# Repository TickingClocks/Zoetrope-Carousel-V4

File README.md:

# Zoetrope-Carousel-V4
repository for the Zoetrope Carousel V4

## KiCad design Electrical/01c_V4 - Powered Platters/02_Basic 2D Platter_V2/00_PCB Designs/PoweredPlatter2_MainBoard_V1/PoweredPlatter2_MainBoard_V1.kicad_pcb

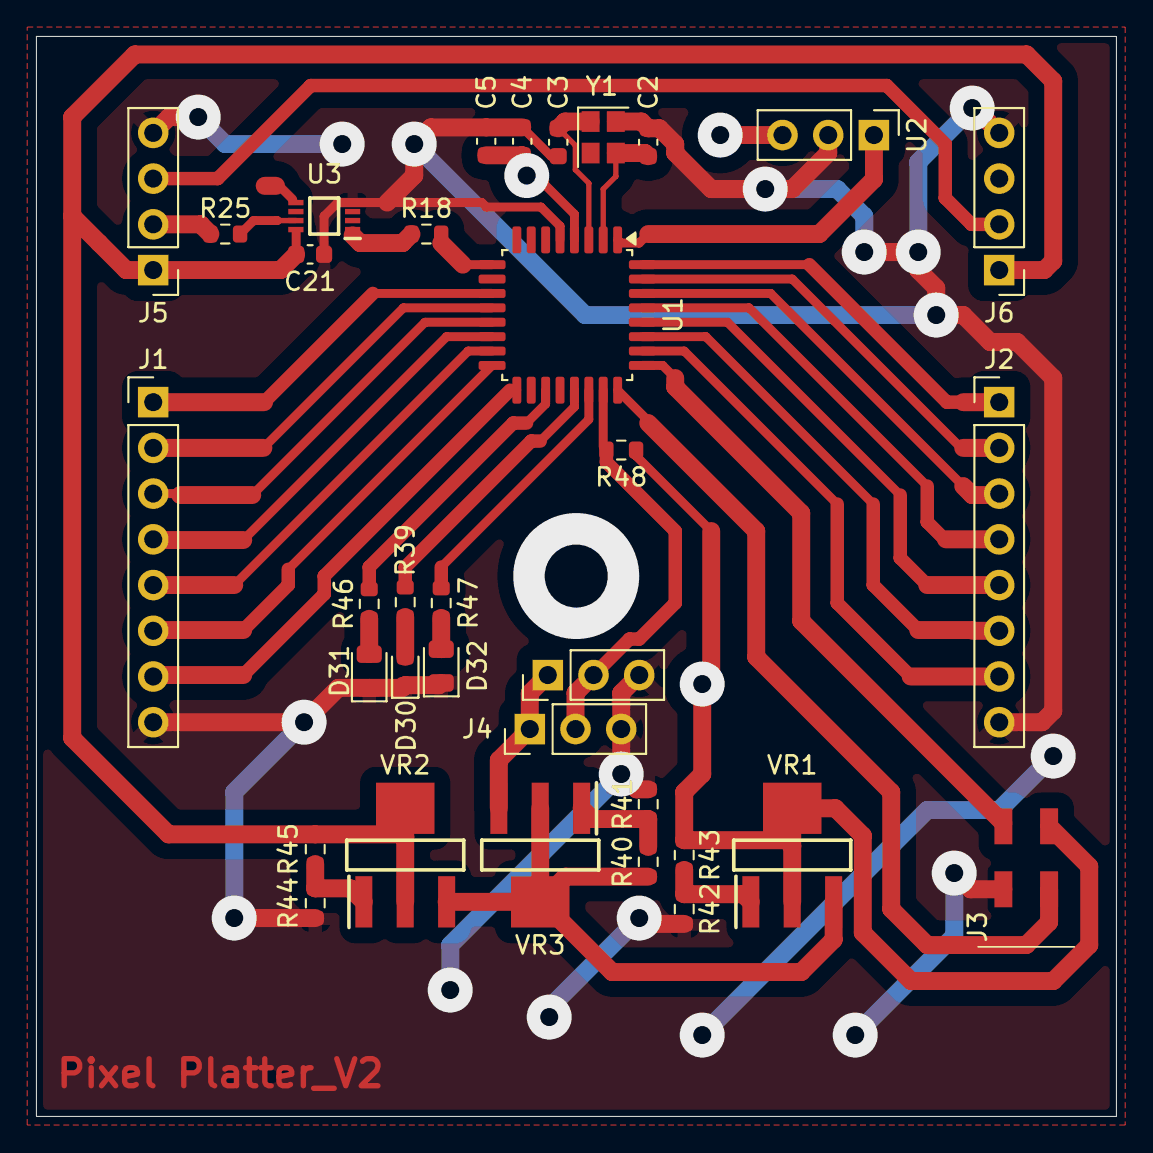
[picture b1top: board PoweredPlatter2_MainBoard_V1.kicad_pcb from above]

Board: 4 copper layers, 60.0 x 60.0 mm, 34 parts (0 on the bottom side), 39 nets.

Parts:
C2, C3: 16pF_0603; C_0603_1608Metric
C4: 4.7uF_0603; C_0603_1608Metric
C5: 1uF_0603; C_0603_1608Metric
C21: 0.1uF_0603; C_0603_1608Metric
D30: LED_0603_BLUE; LED_0603_1608Metric
D31: LED_0805_RED; LED_0805_2012Metric
D32: LED_0805_GREEN; LED_0805_2012Metric
J1, J2: Conn_01x08; PinHeader_1x08_P2.54mm_Vertical
J3: M20-7920242R
J4, J5#2: Conn_01x03; PinHeader_1x03_P2.54mm_Vertical
J5, J6: Conn_01x04; PinHeader_1x04_P2.54mm_Vertical
R18, R25, R44: 300ohm_0603; R_0603_1608Metric
R39, R46, R47: 1kohm_0603; R_0603_1608Metric
R40, R43, R45: 100ohm_0603; R_0603_1608Metric
R41: 620ohm_0603; R_0603_1608Metric
R42: 150ohm_0603; R_0603_1608Metric
R48: 10kohm_0603; R_0603_1608Metric
U1: STM32C071KBTx; LQFP-32_7x7mm_P0.8mm
U2: IR_Receiver; PinHeader_1x03_P2.54mm_Vertical
U3: 74HC3G34DC
VR1, VR2, VR3: LD1117SC-R
Y1: 16Mhz, 3.2 x 2.5; crystal_gnd24

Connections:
+3V3: C4.1, C5.1, J3.1, R43.1, R48.2, U1.4 (VDD), U2.3, VR1.2 (VOUT_1), VR1.4 (VOUT_2)
+5V: C21.1, J5.1, J6.1, R45.1, U3.8 (VCC), VR2.2 (VOUT_1), VR2.4 (VOUT_2)
+9V: R40.1, VR1.3 (VIN), VR2.3 (VIN), VR3.2 (VOUT_1), VR3.4 (VOUT_2)
+12V: J4.1, J5#2.1, VR3.3 (VIN)
/Connectors/neopixelOutIn: J5.3, J6.2
GND: C2.2, C3.1, C4.2, C5.2, C21.2, D30.1 (K), D31.1 (K), D32.1 (K), J1.8, J2.8, J3.4, J4.3, J5.4, J5#2.3, J6.4, R41.2, R42.2, R44.2, U1.5 (VSS), U2.2, U3.4 (GND), Y1.4
IR_input: U1.1 (PB9), U2.1
unnamed: D30.2 (A), R39.1
unnamed: D31.2 (A), R46.1
unnamed: D32.2 (A), R47.1
unnamed: R18.1, U3.1 (1A)
unnamed: R25.2, U3.7 (1Y)
unnamed: R42.1, R43.2, VR1.1 (ADJ)
unnamed: R44.1, R45.2, VR2.1 (ADJ)
unnamed: R40.2, R41.1, VR3.1 (ADJ)
STM32_PH0: C2.1, U1.2 (PC14), Y1.3
STM32_PH1: C3.2, U1.3 (PC15), Y1.1
SWCLK: J3.3, U1.25 (PA14)
SWDIO: J3.2, U1.24 (PA13)
bladeLED1: J1.1, U1.11 (PA4)
bladeLED2: J1.2, U1.12 (PA5)
bladeLED3: J1.3, U1.13 (PA6)
bladeLED4: J1.4, U1.14 (PA7)
bladeLED5: J1.5, U1.15 (PB0)
bladeLED6: J1.6, U1.16 (PB1)
bladeLED7: J1.7, U1.17 (PB2)
bladeLED8: J2.7, U1.26 (PA15)
bladeLED9: J2.6, U1.27 (PB3)
bladeLED10: J2.5, U1.28 (PB4)
bladeLED11: J2.4, U1.29 (PB5)
bladeLED12: J2.3, U1.30 (PB6)
bladeLED13: J2.2, U1.31 (PB7)
bladeLED14: J2.1, U1.32 (PB8)
neopixels_3v3: R18.2, U1.9 (PA2)
neopixels_5v: J5.2, R25.1
strobe: J4.2, J5#2.2, R48.1, U1.23 (PA12)
testLED: R39.2, U1.21 (PA10)
testLED2: R46.2, U1.19 (PA9)
testLED3: R47.2, U1.22 (PA11)

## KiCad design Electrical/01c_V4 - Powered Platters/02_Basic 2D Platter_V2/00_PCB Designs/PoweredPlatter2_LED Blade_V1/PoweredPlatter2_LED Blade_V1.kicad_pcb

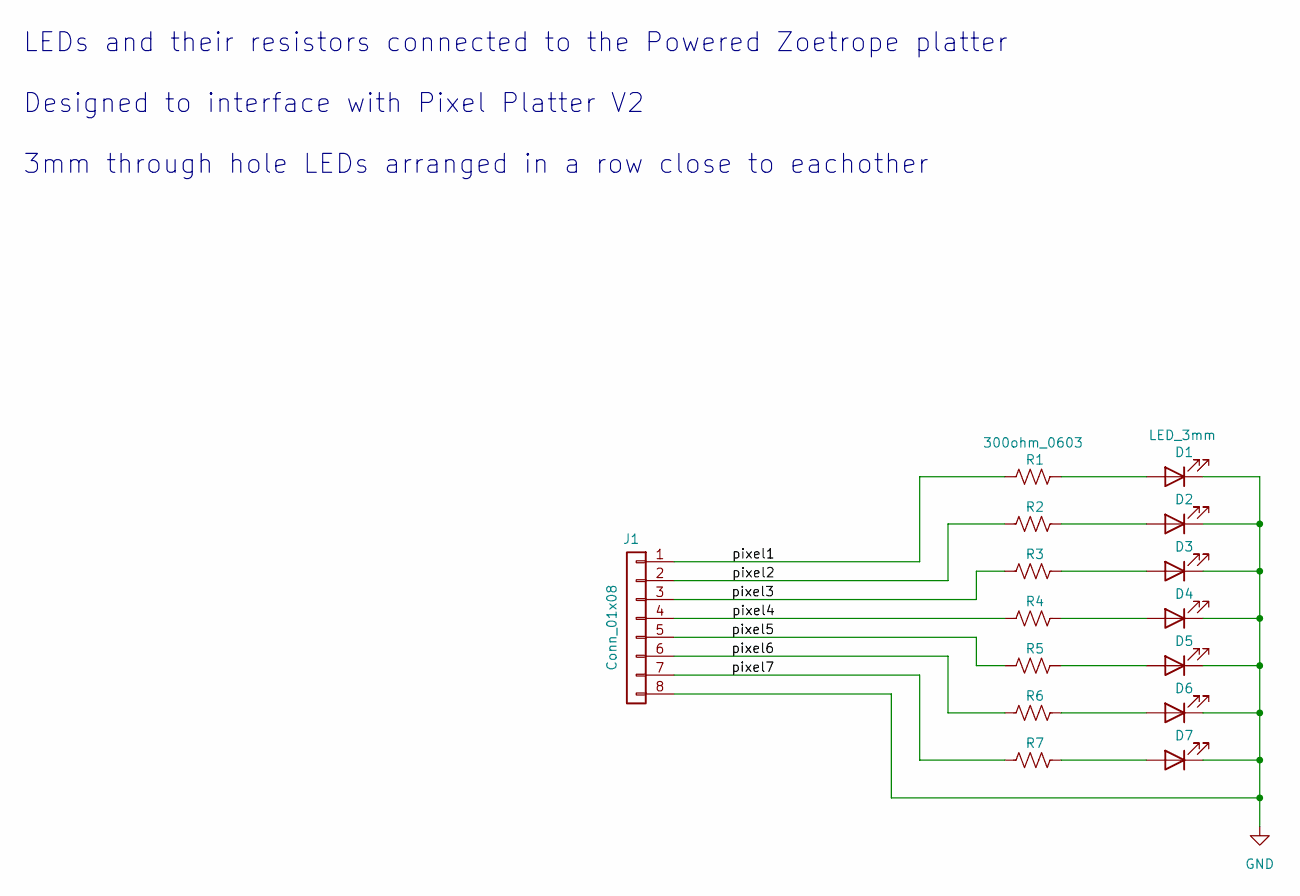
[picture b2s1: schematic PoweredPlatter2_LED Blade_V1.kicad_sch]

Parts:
D1, D2, D3, D4, D5, D6, D7: LED_3mm; LED_D3.0mm
J1: Conn_01x08; PinHeader_1x08_P2.54mm_Vertical
R1, R2, R3, R4, R5, R6, R7: 300ohm_0603; R_0603_1608Metric_Pad0.98x0.95mm_HandSolder

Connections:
/pixel1: J1.1, R1.1
/pixel2: J1.2, R2.1
/pixel3: J1.3, R3.1
/pixel4: J1.4, R4.1
/pixel5: J1.5, R5.1
/pixel6: J1.6, R6.1
/pixel7: J1.7, R7.1
GND: D1.1 (K), D2.1 (K), D3.1 (K), D4.1 (K), D5.1 (K), D6.1 (K), D7.1 (K), J1.8
unnamed: D1.2 (A), R1.2
unnamed: D2.2 (A), R2.2
unnamed: D3.2 (A), R3.2
unnamed: D4.2 (A), R4.2
unnamed: D5.2 (A), R5.2
unnamed: D6.2 (A), R6.2
unnamed: D7.2 (A), R7.2

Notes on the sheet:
LEDs and their resistors connected to the Powered Zoetrope platter Designed to interface with Pixel Platter V2 3mm through hole LEDs arranged in a row close to eachother

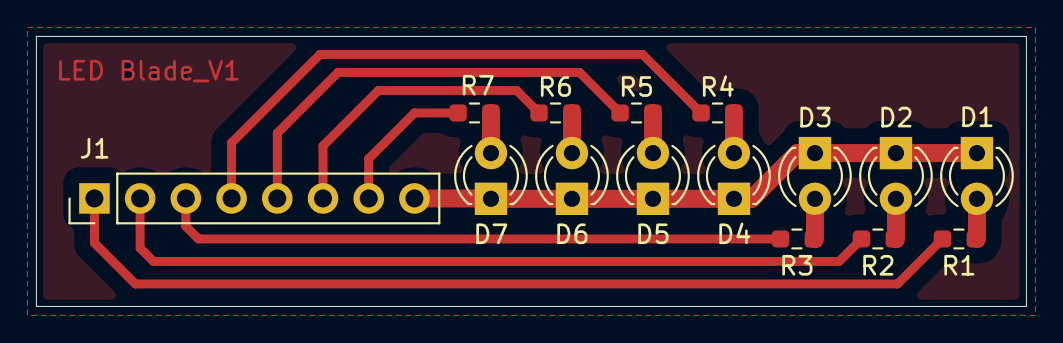
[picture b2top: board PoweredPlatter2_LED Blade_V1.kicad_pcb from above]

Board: 2 copper layers, 55.0 x 15.0 mm, 15 parts (0 on the bottom side), 15 nets.

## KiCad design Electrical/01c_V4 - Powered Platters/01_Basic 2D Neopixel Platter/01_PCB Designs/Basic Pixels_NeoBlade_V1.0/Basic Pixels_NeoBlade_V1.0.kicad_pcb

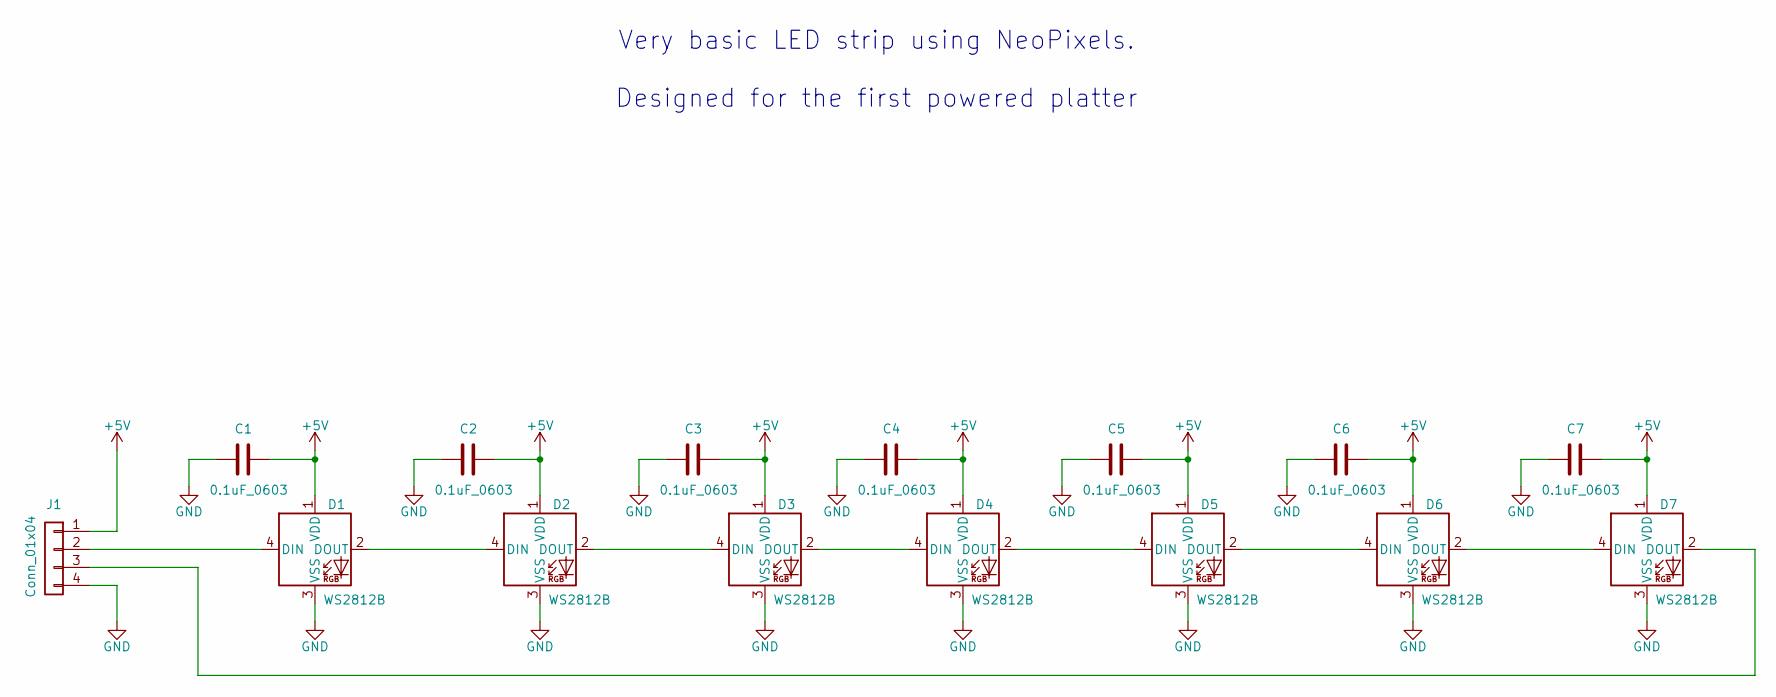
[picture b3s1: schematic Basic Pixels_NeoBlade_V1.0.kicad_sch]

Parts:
C1, C2, C3, C4, C5, C6, C7: 0.1uF_0603; C_0603_1608Metric
D1, D2, D3, D4, D5, D6, D7: WS2812B; LED_WS2812B_PLCC4_5.0x5.0mm_P3.2mm
J1: Conn_01x04; PinHeader_1x04_P2.54mm_Vertical

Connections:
+5V: C1.1, C2.1, C3.1, C4.1, C5.1, C6.1, C7.1, D1.1 (VDD), D2.1 (VDD), D3.1 (VDD), D4.1 (VDD), D5.1 (VDD), D6.1 (VDD), D7.1 (VDD), J1.1
GND: C1.2, C2.2, C3.2, C4.2, C5.2, C6.2, C7.2, D1.3 (VSS), D2.3 (VSS), D3.3 (VSS), D4.3 (VSS), D5.3 (VSS), D6.3 (VSS), D7.3 (VSS), J1.4
unnamed: D1.4 (DIN), J1.2
unnamed: D1.2 (DOUT), D2.4 (DIN)
unnamed: D2.2 (DOUT), D3.4 (DIN)
unnamed: D3.2 (DOUT), D4.4 (DIN)
unnamed: D4.2 (DOUT), D5.4 (DIN)
unnamed: D5.2 (DOUT), D6.4 (DIN)
unnamed: D6.2 (DOUT), D7.4 (DIN)
unnamed: D7.2 (DOUT), J1.3

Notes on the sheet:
Very basic LED strip using NeoPixels. Designed for the first powered platter

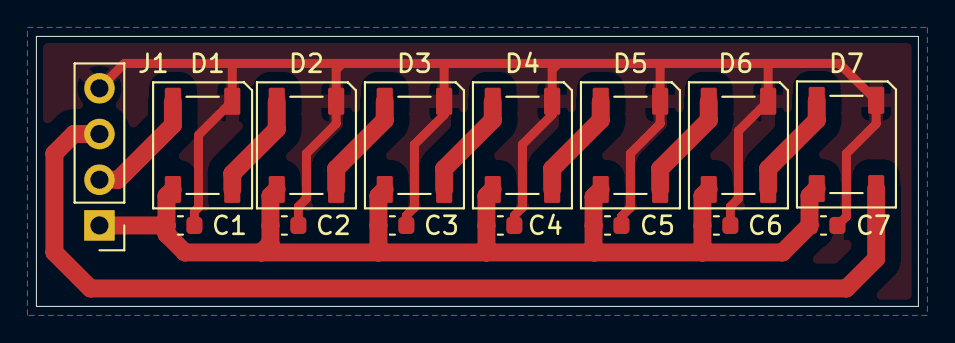
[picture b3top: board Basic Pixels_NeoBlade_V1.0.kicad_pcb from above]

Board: 2 copper layers, 49.0 x 15.0 mm, 15 parts (0 on the bottom side), 10 nets.

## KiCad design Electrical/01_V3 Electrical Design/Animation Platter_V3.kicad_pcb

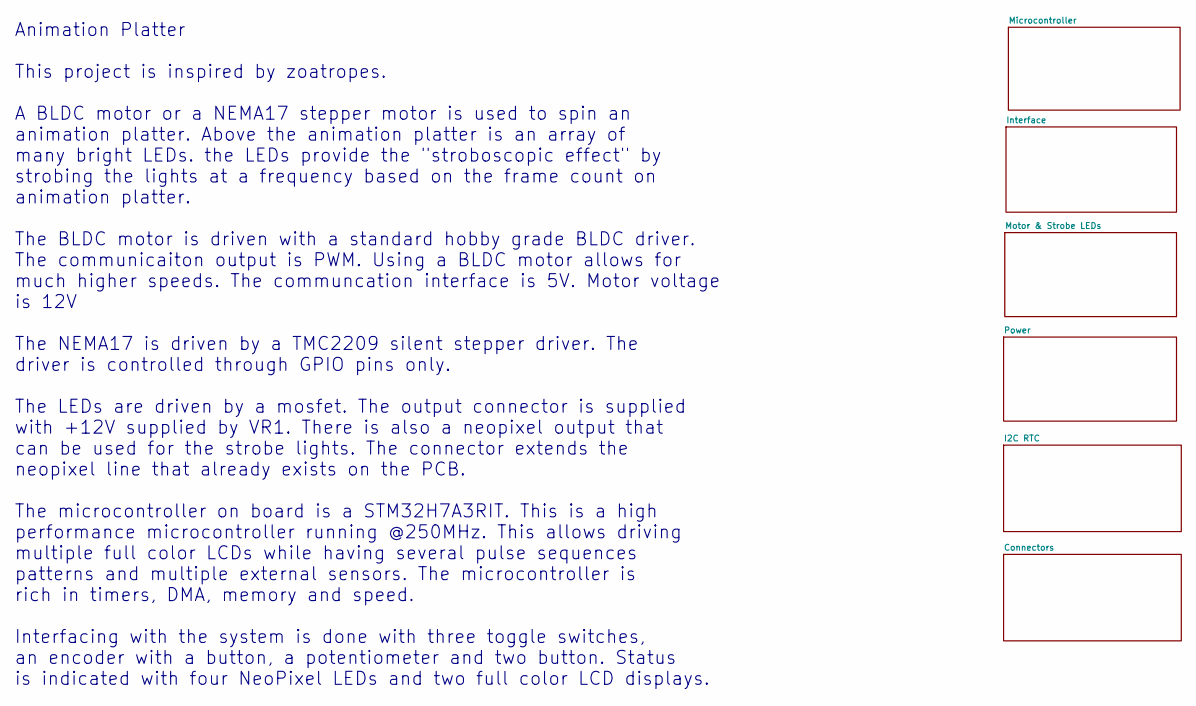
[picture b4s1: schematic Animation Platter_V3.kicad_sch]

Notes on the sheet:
Animation Platter This project is inspired by zoatropes. A BLDC motor or a NEMA17 stepper motor is used to spin an animation platter. Above the animation platter is an array of many bright LEDs. the LEDs provide the "stroboscopic effect" by strobing the lights at a frequency based on the frame coun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

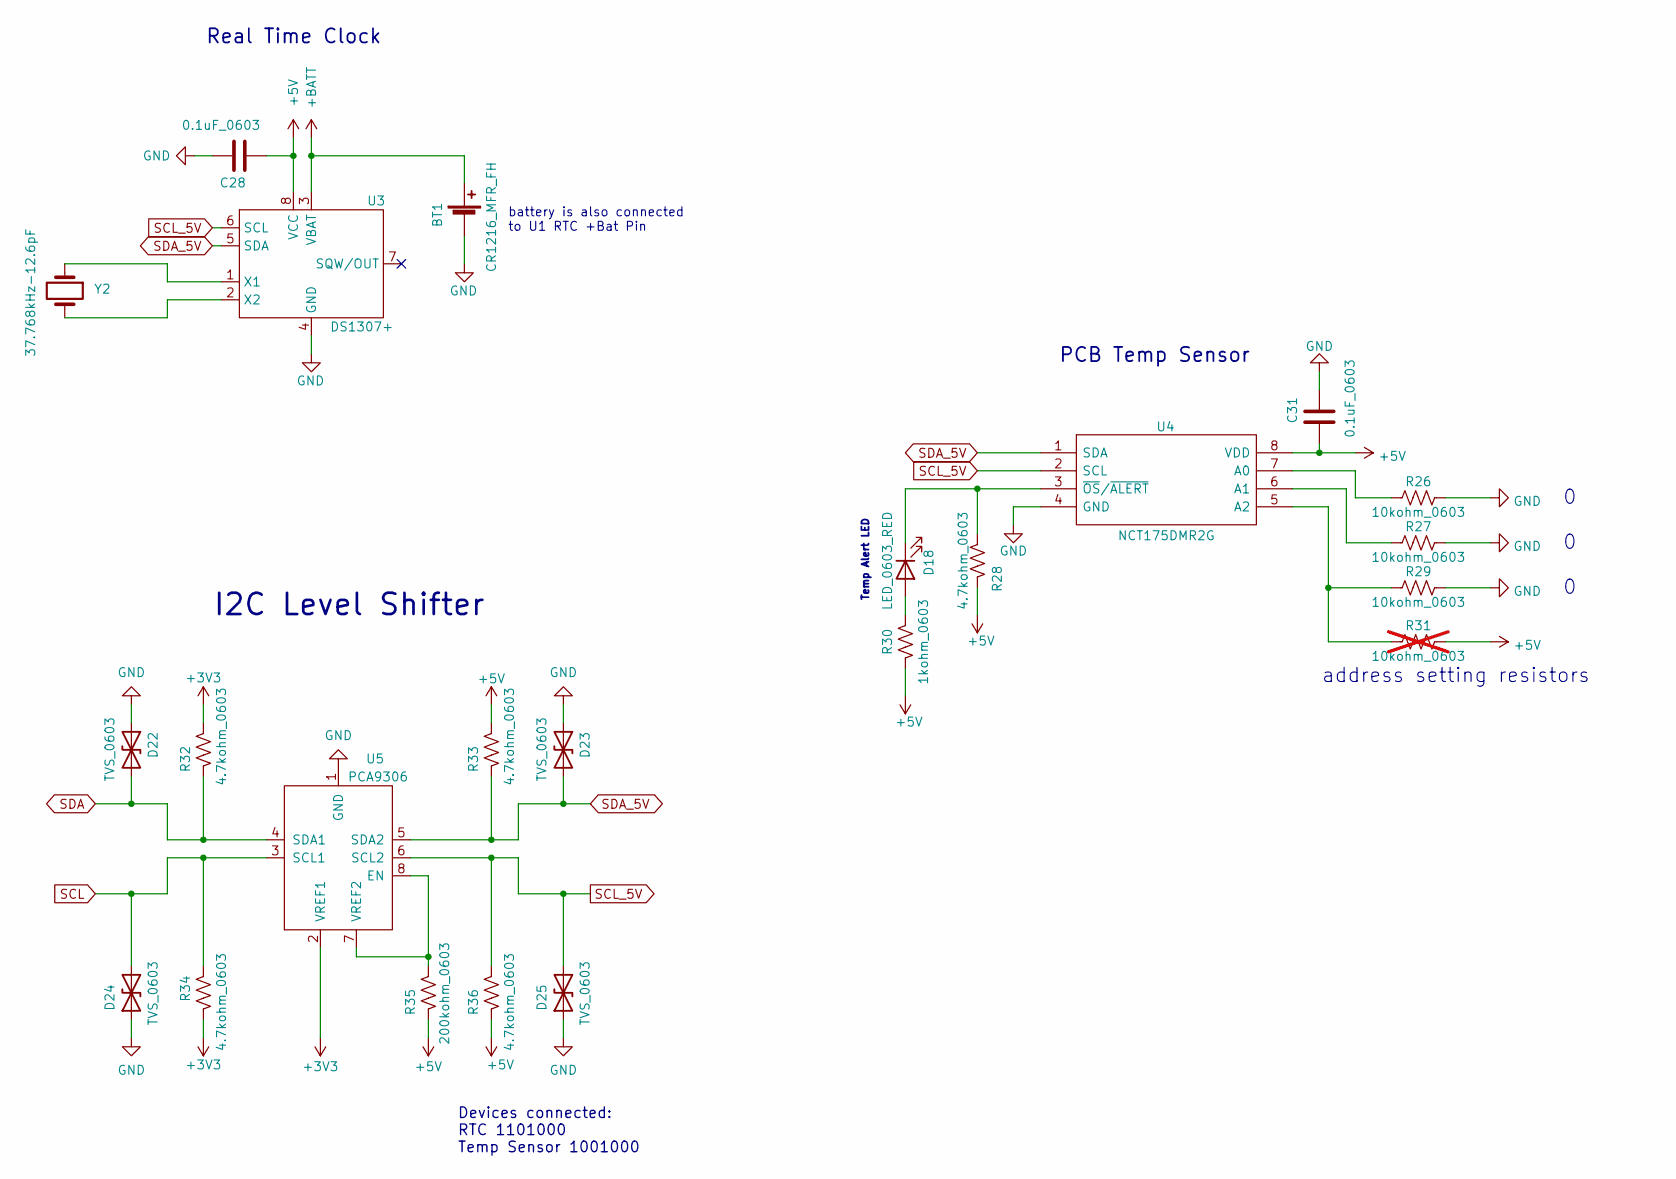
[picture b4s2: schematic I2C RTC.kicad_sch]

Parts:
BT1: CR1216_MFR_FH; CR2032_SMT
C28, C31: 0.1uF_0603; C_0603_1608Metric
D18: LED_0603_RED; LED_0603_1608Metric
D22, D23, D24, D25: TVS_0603; R_0603_1608Metric
R26, R27, R29: 10kohm_0603; R_0603_1608Metric
R28, R32, R33, R34, R36: 4.7kohm_0603; R_0603_1608Metric
R30: 1kohm_0603; R_0603_1608Metric
R31: 10kohm_0603; R_0603_1608Metric; not fitted
R35: 200kohm_0603; R_0603_1608Metric
U3: DS1307+; DS1307
U4: NCT175DMR2G; Mouser Part Number 863-NCT175DMR2G
U5: PCA9306
Y2: 37.768kHz-12.6pF; 37.768kHz

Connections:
+BATT: BT1.1, BT1.3, U3.3 (VBAT); also elsewhere on the board
unnamed: D18.2 (A), R30.1
unnamed: D18.1 (K), R28.2, U4.3 (~OS/~ALERT)
unnamed: U3.1 (X1), Y2.1
unnamed: U3.2 (X2), Y2.2
unnamed: R26.1, U4.7 (A0)
unnamed: R27.1, U4.6 (A1)
unnamed: R29.1, R31.1, U4.5 (A2)
unnamed: R35.2, U5.7 (VREF2), U5.8 (EN)
SCL: D24.2 (A2), R34.2, U5.3 (SCL1); also elsewhere on the board
SCL_5V: D25.2 (A2), R36.2, U3.6 (SCL), U4.2 (SCL), U5.6 (SCL2)
SDA: D22.2 (A2), R32.1, U5.4 (SDA1); also elsewhere on the board
SDA_5V: D23.2 (A2), R33.1, U3.5 (SDA), U4.1 (SDA), U5.5 (SDA2)

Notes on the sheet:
Real Time Clock
Devices connected: RTC 1101000 Temp Sensor 1001000
address setting resistors
I2C Level Shifter
battery is also connected to U1 RTC +Bat Pin
PCB Temp Sensor
Temp Alert LED

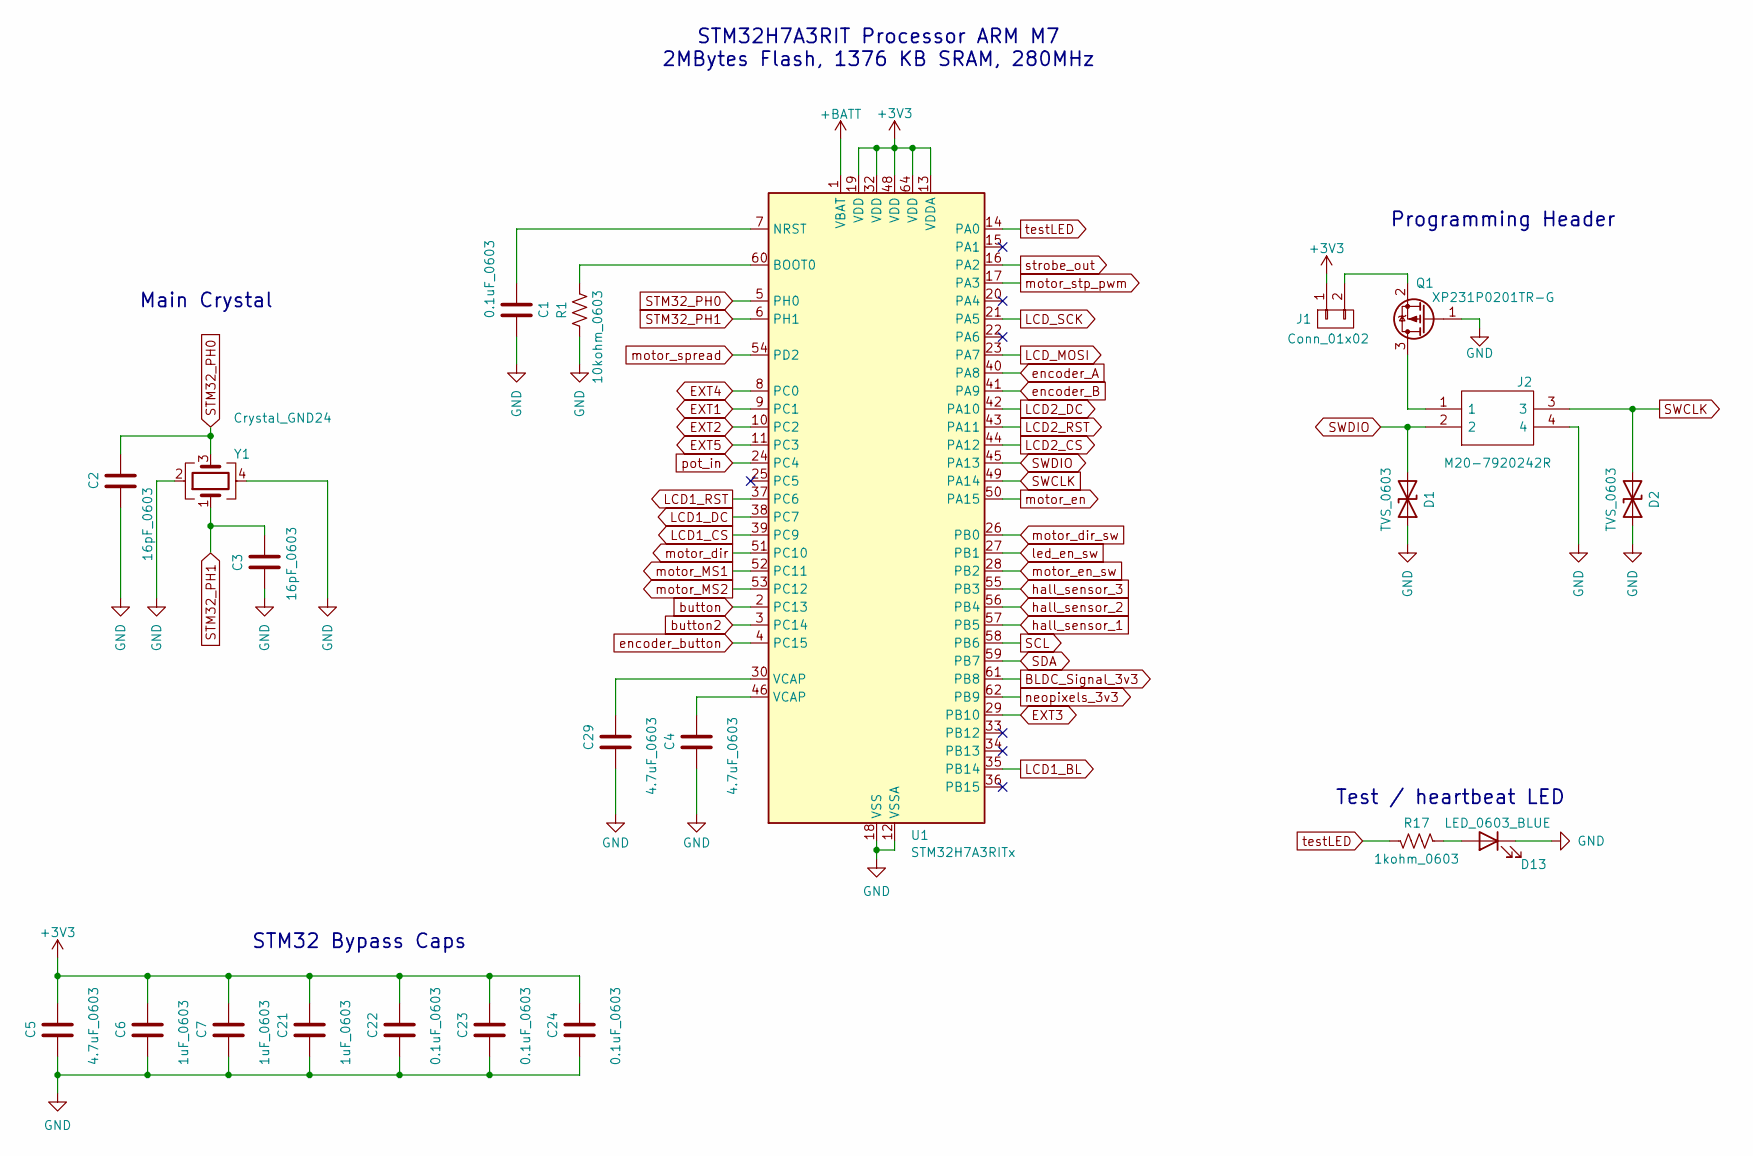
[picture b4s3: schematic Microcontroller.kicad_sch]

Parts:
C1, C22, C23, C24: 0.1uF_0603; C_0603_1608Metric
C2, C3: 16pF_0603; C_0603_1608Metric
C4, C5, C29: 4.7uF_0603; C_0603_1608Metric
C6, C7, C21: 1uF_0603; C_0603_1608Metric
D1, D2: TVS_0603; R_0603_1608Metric
D13: LED_0603_BLUE; LED_0603_1608Metric
J1: Conn_01x02; PinHeader_1x02_P2.54mm_Vertical
J2: M20-7920242R; M207920242R; Mouser Part Number 855-M20-7920242R
Q1: XP231P0201TR-G; SOT95P240X115-3N
R1: 10kohm_0603; R_0603_1608Metric
R17: 1kohm_0603; R_0603_1608Metric
U1: STM32H7A3RITx; LQFP-64_10x10mm_P0.5mm
Y1: Crystal_GND24; crystal_gnd24

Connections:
+BATT: U1.1 (VBAT); also elsewhere on the board
EXT1: U1.9 (PC1); also elsewhere on the board
EXT2: U1.10 (PC2); also elsewhere on the board
EXT3: U1.29 (PB10); also elsewhere on the board
EXT4: U1.8 (PC0); also elsewhere on the board
EXT5: U1.11 (PC3); also elsewhere on the board
LCD1_BL: U1.35 (PB14); also elsewhere on the board
LCD1_CS: U1.39 (PC9); also elsewhere on the board
LCD1_DC: U1.38 (PC7); also elsewhere on the board
LCD1_RST: U1.37 (PC6); also elsewhere on the board
LCD2_CS: U1.44 (PA12); also elsewhere on the board
LCD2_DC: U1.42 (PA10); also elsewhere on the board
LCD2_RST: U1.43 (PA11); also elsewhere on the board
LCD_MOSI: U1.23 (PA7); also elsewhere on the board
LCD_SCK: U1.21 (PA5); also elsewhere on the board
unnamed: C4.1, U1.46 (VCAP)
unnamed: C29.1, U1.30 (VCAP)
unnamed: J2.1, Q1.3 (D)
unnamed: R1.2, U1.60 (BOOT0)
unnamed: C1.1, U1.7 (NRST)
SCL: U1.58 (PB6); also elsewhere on the board
SDA: U1.59 (PB7); also elsewhere on the board
STM32_PH0: C2.1, U1.5 (PH0), Y1.3
STM32_PH1: C3.2, U1.6 (PH1), Y1.1
SWCLK: D2.2 (A2), J2.3, U1.49 (PA14)
SWDIO: D1.2 (A2), J2.2, U1.45 (PA13)
button: U1.2 (PC13); also elsewhere on the board
button2: U1.3 (PC14); also elsewhere on the board
encoder_A: U1.40 (PA8); also elsewhere on the board
encoder_B: U1.41 (PA9); also elsewhere on the board
encoder_button: U1.4 (PC15); also elsewhere on the board
hall_sensor_1: U1.57 (PB5); also elsewhere on the board
hall_sensor_2: U1.56 (PB4); also elsewhere on the board
hall_sensor_3: U1.55 (PB3); also elsewhere on the board
led_en_sw: U1.27 (PB1); also elsewhere on the board
motor_MS1: U1.52 (PC11); also elsewhere on the board
motor_MS2: U1.53 (PC12); also elsewhere on the board
motor_dir: U1.51 (PC10); also elsewhere on the board
motor_dir_sw: U1.26 (PB0); also elsewhere on the board
motor_en: U1.50 (PA15); also elsewhere on the board
motor_en_sw: U1.28 (PB2); also elsewhere on the board
motor_spread: U1.54 (PD2); also elsewhere on the board
motor_stp_pwm: U1.17 (PA3); also elsewhere on the board
neopixels_3v3: U1.62 (PB9); also elsewhere on the board
pot_in: U1.24 (PC4); also elsewhere on the board
strobe_out: U1.16 (PA2); also elsewhere on the board
testLED: R17.2, U1.14 (PA0)

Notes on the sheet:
STM32 Bypass Caps
Test / heartbeat LED
STM32H7A3RIT Processor ARM M7 2MBytes Flash, 1376 KB SRAM, 280MHz
Main Crystal
Programming Header

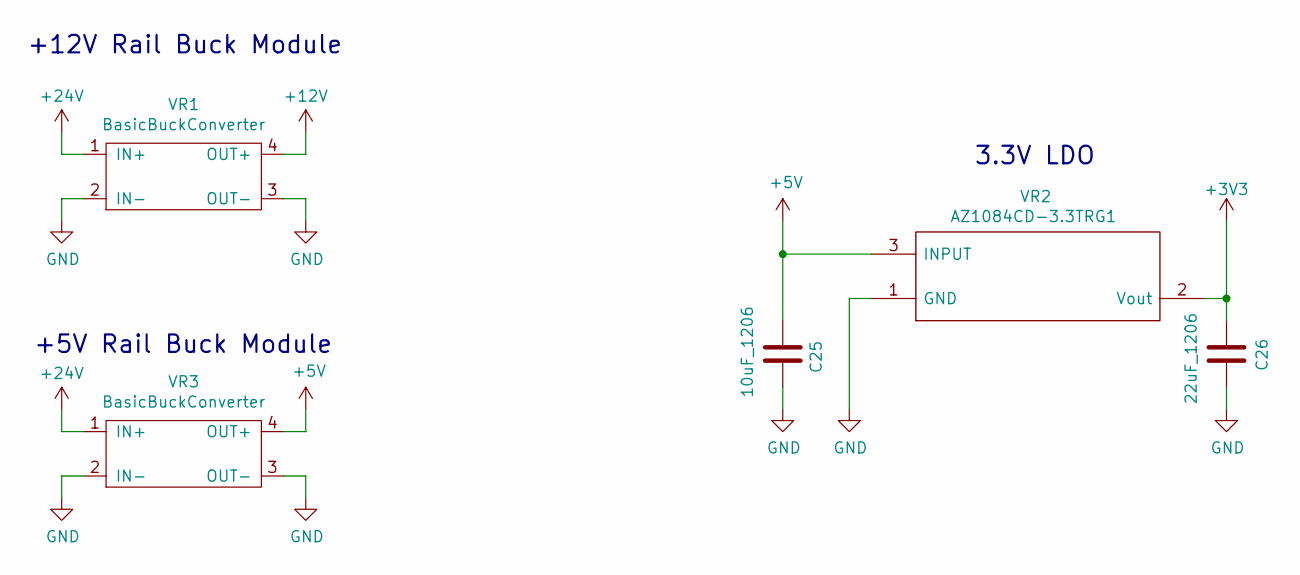
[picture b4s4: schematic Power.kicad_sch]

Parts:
C25: 10uF_1206; C_1206_3216Metric
C26: 22uF_1206; C_1206_3216Metric
VR1, VR3: BasicBuckConverter; LM2596_Module(43mmx21mm)
VR2: AZ1084CD-3.3TRG1; AZ1084CD33TRG1

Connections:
+12V: VR1.4 (OUT+); also elsewhere on the board
+24V: VR1.1 (IN+), VR3.1 (IN+); also elsewhere on the board

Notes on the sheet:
+12V Rail Buck Module
+5V Rail Buck Module
3.3V LDO

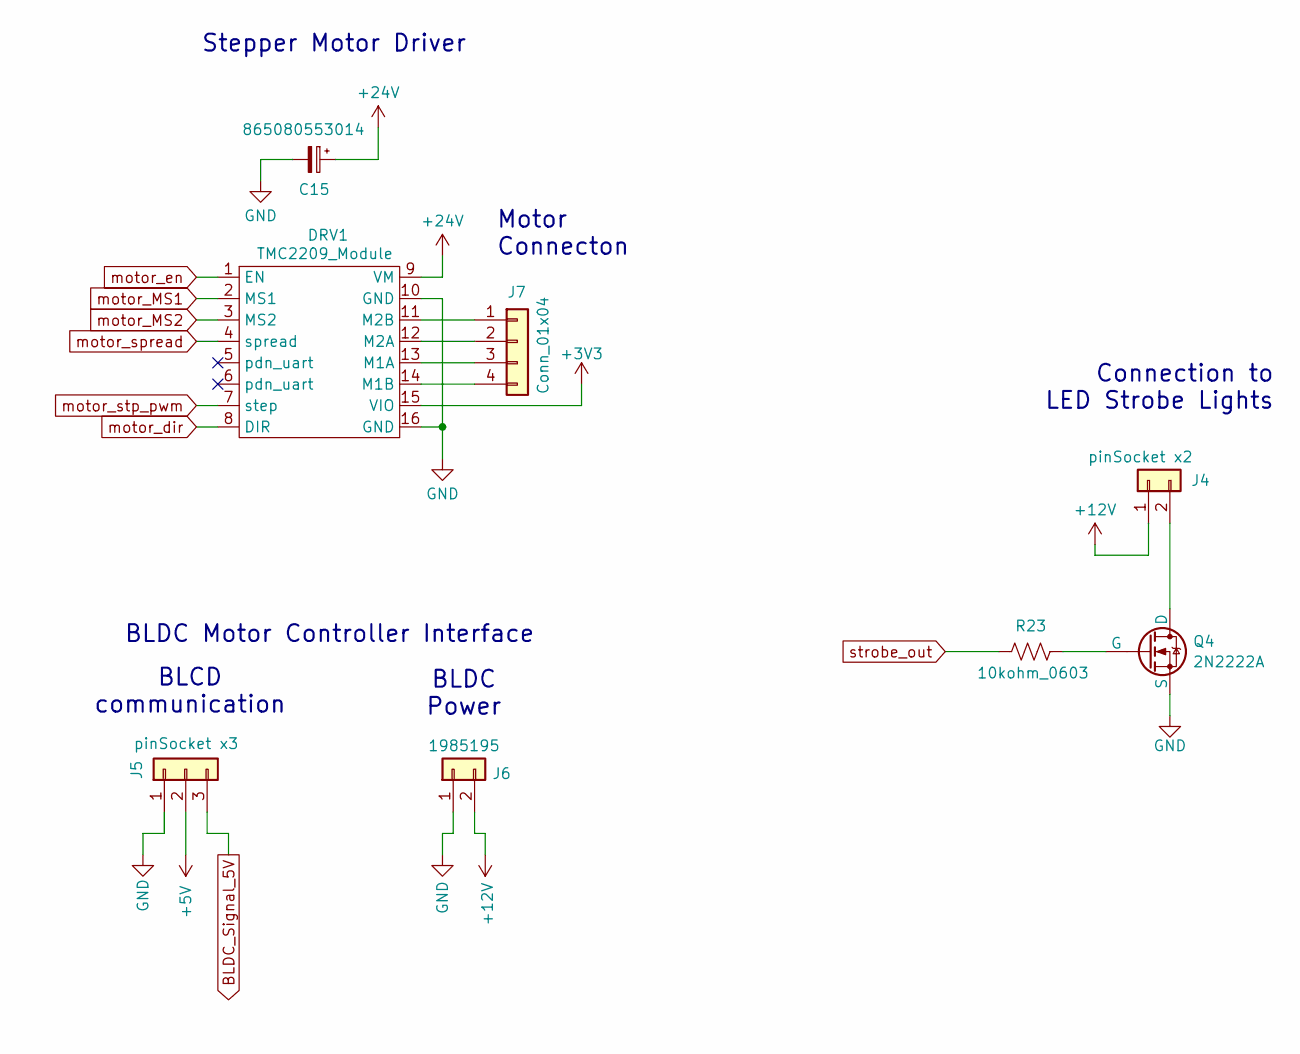
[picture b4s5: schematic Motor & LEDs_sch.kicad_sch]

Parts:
C15: 865080553014; CAPAE830X1050N
DRV1: TMC2209_Module
J4: pinSocket x2; PinSocket_1x02_P2.54mm_Vertical
J5: pinSocket x3; PinSocket_1x03_P2.54mm_Vertical
J6: 1985195
J7: Conn_01x04; PinHeader_1x04_P2.54mm_Vertical
Q4: 2N2222A; TO-92
R23: 10kohm_0603; R_0603_1608Metric

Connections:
+12V: J4.1, J6.2; also elsewhere on the board
+24V: C15.1, DRV1.9 (VM); also elsewhere on the board
unnamed: DRV1.13 (M1A), J7.3
unnamed: DRV1.14 (M1B), J7.4
unnamed: DRV1.12 (M2A), J7.2
unnamed: DRV1.11 (M2B), J7.1
unnamed: J4.2, Q4.3 (D)
unnamed: Q4.2 (G), R23.2
motor_MS1: DRV1.2 (MS1); also elsewhere on the board
motor_MS2: DRV1.3 (MS2); also elsewhere on the board
motor_dir: DRV1.8 (DIR); also elsewhere on the board
motor_en: DRV1.1 (EN); also elsewhere on the board
motor_spread: DRV1.4 (spread); also elsewhere on the board
motor_stp_pwm: DRV1.7 (step); also elsewhere on the board
strobe_out: R23.1; also elsewhere on the board

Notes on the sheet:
Stepper Motor Driver
Connection to LED Strobe Lights
BLDC Motor Controller Interface
Motor Connecton
BLDC Power
BLCD communication

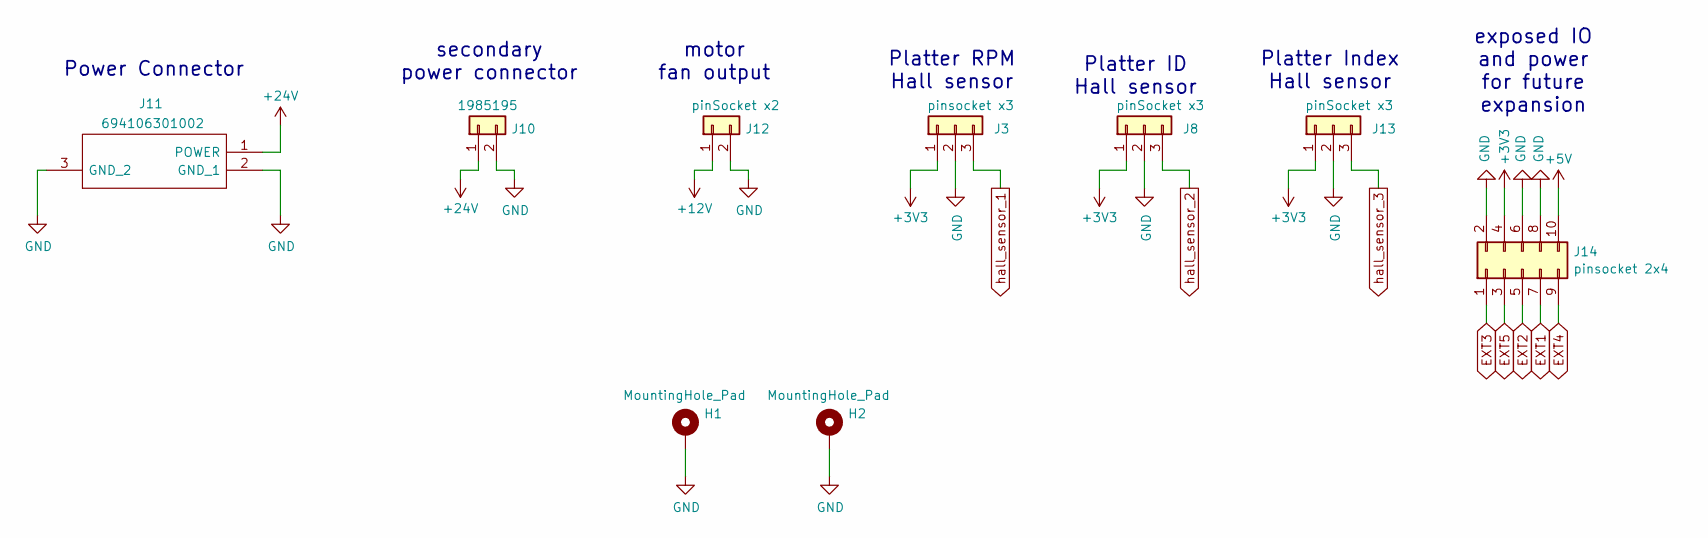
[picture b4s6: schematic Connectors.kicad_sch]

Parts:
H1, H2: MountingHole_Pad; 3mm_MH
J3: pinsocket x3; PinSocket_1x03_P2.54mm_Vertical
J8, J13: pinSocket x3; PinSocket_1x03_P2.54mm_Vertical
J10: 1985195
J11: 694106301002; 694106301002_1; Mouser Part Number 710-694106301002
J12: pinSocket x2; PinSocket_1x02_P2.54mm_Vertical
J14: pinsocket 2x4; PinSocket_2x05_P2.54mm_Vertical

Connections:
+12V: J12.1; also elsewhere on the board
+24V: J10.1, J11.1 (POWER); also elsewhere on the board
EXT1: J14.7; also elsewhere on the board
EXT2: J14.5; also elsewhere on the board
EXT3: J14.1; also elsewhere on the board
EXT4: J14.9; also elsewhere on the board
EXT5: J14.3; also elsewhere on the board
hall_sensor_1: J3.3; also elsewhere on the board
hall_sensor_2: J8.3; also elsewhere on the board
hall_sensor_3: J13.3; also elsewhere on the board

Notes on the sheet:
Platter ID Hall sensor
secondary power connector
exposed IO and power for future expansion
Platter RPM Hall sensor
Platter Index Hall sensor
Power Connector
motor fan output

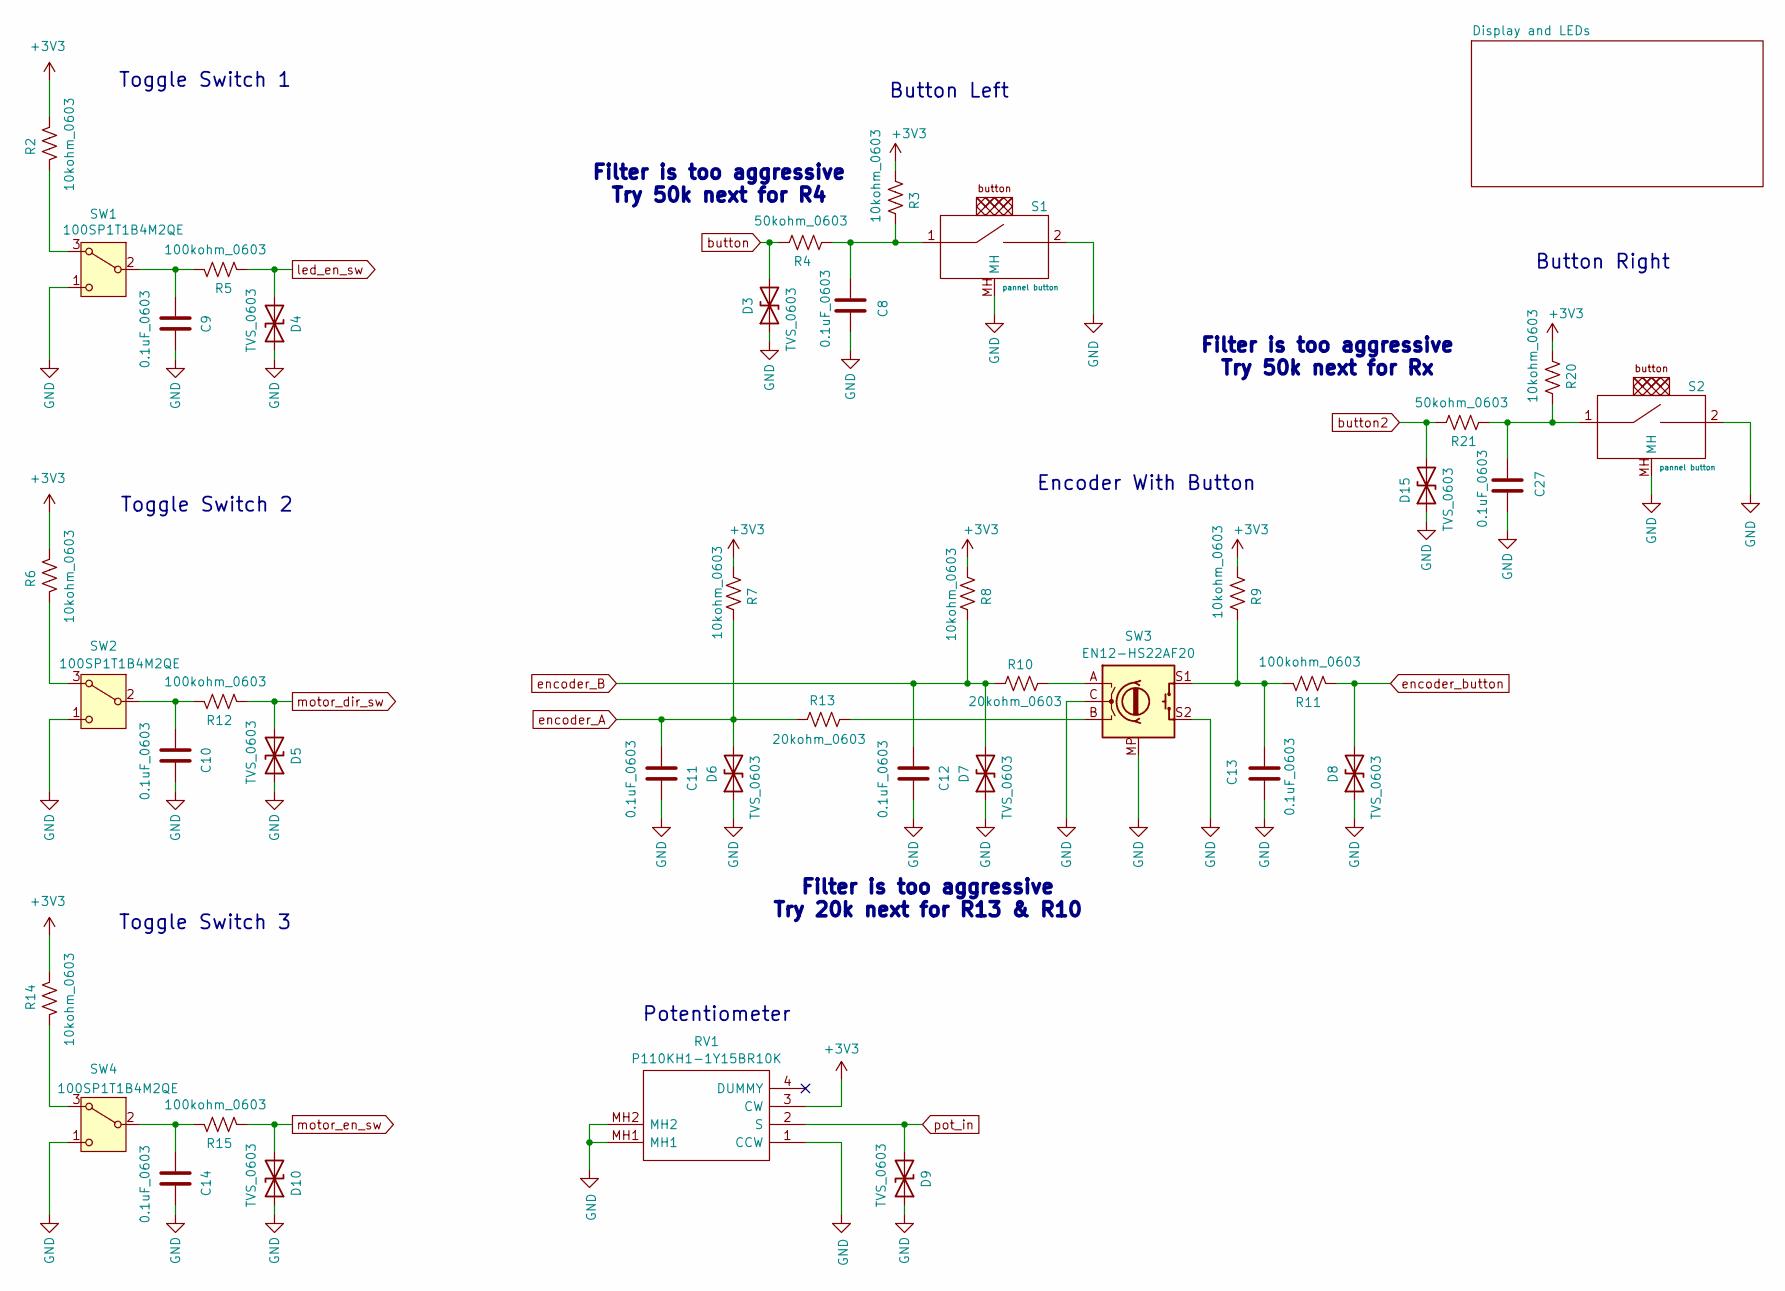
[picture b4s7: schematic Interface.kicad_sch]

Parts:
C8, C9, C10, C11, C12, C13, C14, C27: 0.1uF_0603; C_0603_1608Metric
D3, D4, D5, D6, D7, D8, D9, D10, D15: TVS_0603; R_0603_1608Metric
R2, R3, R6, R7, R8, R9, R14, R20: 10kohm_0603; R_0603_1608Metric
R4, R21: 50kohm_0603; R_0603_1608Metric
R5, R11, R12, R15: 100kohm_0603; R_0603_1608Metric
R10, R13: 20kohm_0603; R_0603_1608Metric
RV1: P110KH1-1Y15BR10K; P110KH11Y15BR10K; Mouser Part Number 858-P110KH11Y15BR10K
S1, S2: pannel button; 10mm_pannel_button2
SW1, SW2, SW4: 100SP1T1B4M2QE
SW3: EN12-HS22AF20; EN12HS22AF20

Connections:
unnamed: C8.1, R3.2, R4.1, S1.1
unnamed: C13.1, R9.2, R11.1, SW3.S1
unnamed: C27.1, R20.2, R21.1, S2.1
unnamed: R10.2, SW3.A
unnamed: R13.2, SW3.B
unnamed: R2.2, SW1.3 (A)
unnamed: C9.2, R5.1, SW1.2 (B)
unnamed: R6.2, SW2.3 (A)
unnamed: C10.2, R12.1, SW2.2 (B)
unnamed: R14.2, SW4.3 (A)
unnamed: C14.2, R15.1, SW4.2 (B)
button: D3.2 (A2), R4.2; also elsewhere on the board
button2: D15.2 (A2), R21.2; also elsewhere on the board
encoder_A: C11.2, D6.2 (A2), R7.2, R13.1; also elsewhere on the board
encoder_B: C12.2, D7.2 (A2), R8.2, R10.1; also elsewhere on the board
encoder_button: D8.2 (A2), R11.2; also elsewhere on the board
led_en_sw: D4.2 (A2), R5.2; also elsewhere on the board
motor_dir_sw: D5.2 (A2), R12.2; also elsewhere on the board
motor_en_sw: D10.2 (A2), R15.2; also elsewhere on the board
pot_in: D9.2 (A2), RV1.2 (S); also elsewhere on the board

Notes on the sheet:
Encoder With Button
Filter is too aggressive Try 20k next for R13 & R10
Filter is too aggressive Try 50k next for R4
Button Left
Toggle Switch 1
Button Right
Potentiometer
Toggle Switch 2
Toggle Switch 3
Filter is too aggressive Try 50k next for Rx
